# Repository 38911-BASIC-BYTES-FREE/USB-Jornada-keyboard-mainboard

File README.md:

Jornada keyboard adapter for using it as a USB HID Keyboard.
Compile it and upload in Arduino choosing Arduino Micro board.
Modification of https://github.com/RasmusB/USB-Keyboard-Adapter .
Used in project https://www.thingiverse.com/thing:6938611 .
PCB project in the folder Jornada_keyboard_mainboard .

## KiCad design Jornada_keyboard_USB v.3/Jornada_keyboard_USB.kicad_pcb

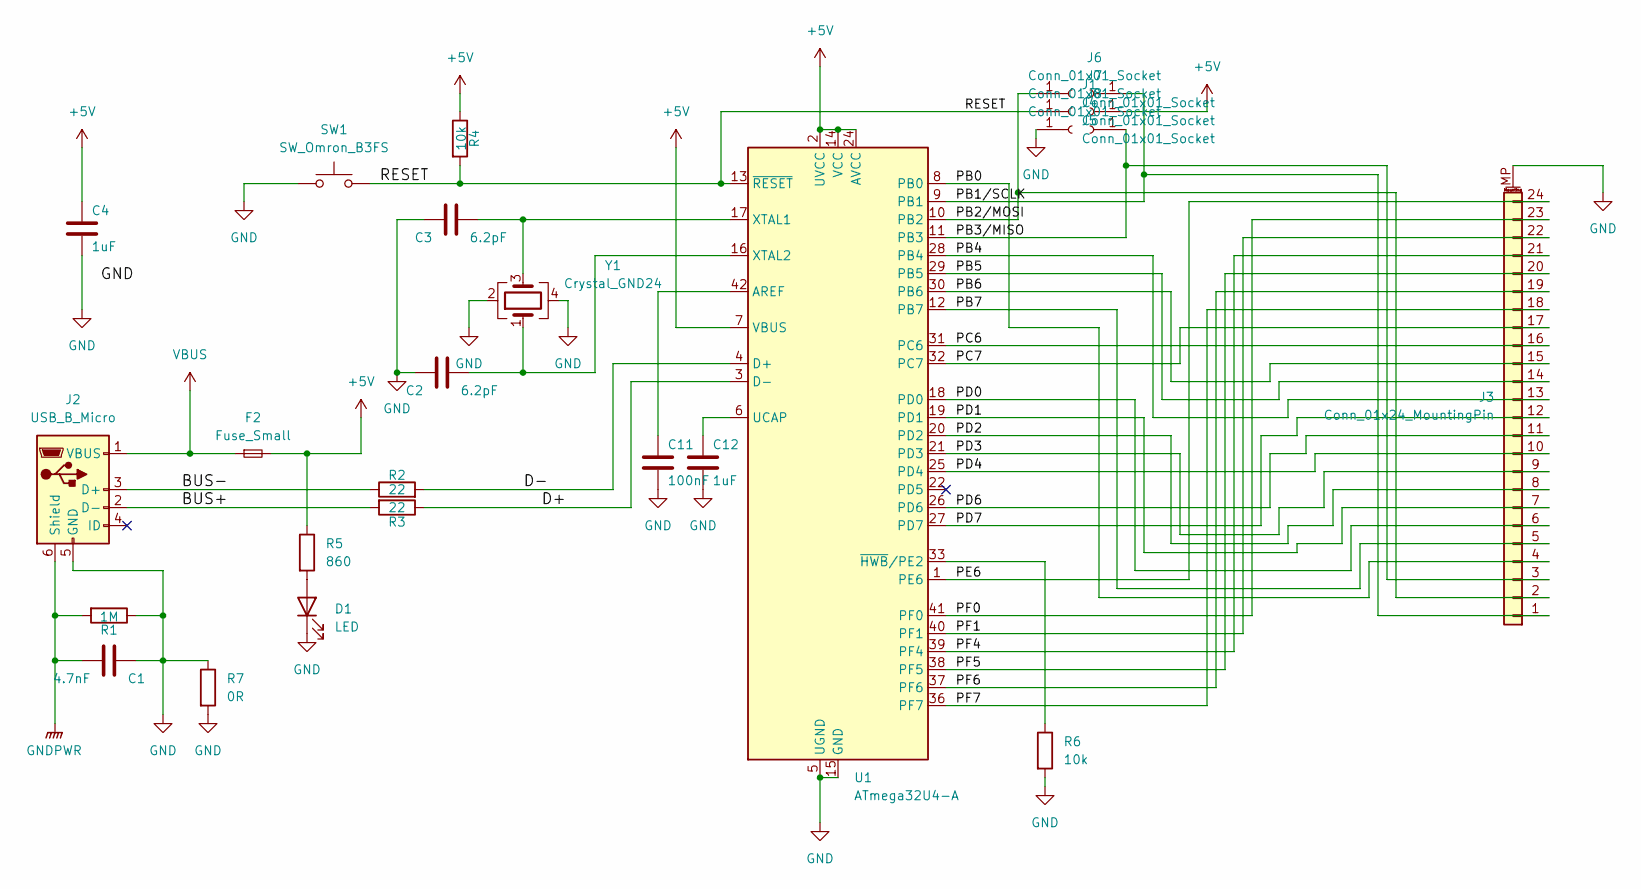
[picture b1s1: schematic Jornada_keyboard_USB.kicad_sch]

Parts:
C1: 4.7nF; C_1206_3216Metric; MPN 0402B472K500NT; JLCPCB C1538
C2, C3: 6.2pF; C_1206_3216Metric; MPN CC0402CRNPO9BN6R2; JLCPCB C325456
C4, C12: 1uF; C_1206_3216Metric; MPN CL05A105KA5NQNC; JLCPCB C52923
C11: 100nF; C_1206_3216Metric; MPN CL05B104KO5NNNC; JLCPCB C1525
D1: LED; LED_1206_3216Metric
F2: Fuse_Small; Fuse_1206_3216Metric
J1, J4, J5, J6, J7, J8: Conn_01x01_Socket; SolderWirePad_1x01_SMD_1x2mm
J2: USB_B_Micro; USB_Micro-B_Amphenol_10104110_Horizontal
J3: Conn_01x24_MountingPin; TE_2-84952-4_1x24-1MP_P1.0mm_Horizontal
R1: 1M; R_1206_3216Metric; MPN 0402WGF1004TCE; JLCPCB C26083
R2, R3: 22; R_1206_3216Metric; MPN 0402WGF220JTCE; JLCPCB C25092
R4: 10k; R_1206_3216Metric; MPN 0402WGF1002TCE; JLCPCB C25744
R5: 860; R_1206_3216Metric
R6: 10k; R_1206_3216Metric
R7: 0R; R_1206_3216Metric
SW1: SW_Omron_B3FS; SW_SPST_PTS645
U1: ATmega32U4-A; TQFP-44_10x10mm_P0.8mm
Y1: Crystal_GND24; Crystal_SMD_3225-4Pin_3.2x2.5mm_HandSoldering

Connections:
+5V: C4.1, F2.2, J7.1, R4.1, R5.1, U1.2 (UVCC), U1.7 (VBUS), U1.14 (VCC), U1.24 (AVCC), U1.34 (VCC), U1.44 (AVCC)
/BUS+: J2.2 (D-), R3.2
/BUS-: J2.3 (D+), R2.1
/D+: R3.1, U1.3 (D-)
/D-: R2.2, U1.4 (D+)
/PB0: J3.4, U1.8 (PB0)
/PB1/SCLK: J3.1, J6.1, U1.9 (PB1)
/PB2/MOSI: J1.1, J3.2, U1.10 (PB2)
/PB3/MISO: J3.3, J8.1, U1.11 (PB3)
/PB4: J3.13, U1.28 (PB4)
/PB5: J3.14, U1.29 (PB5)
/PB6: J3.15, U1.30 (PB6)
/PB7: J3.5, U1.12 (PB7)
/PC6: J3.16, U1.31 (PC6)
/PC7: J3.17, U1.32 (PC7)
/PD0: J3.6, U1.18 (PD0)
/PD1: J3.7, U1.19 (PD1)
/PD2: J3.8, U1.20 (PD2)
/PD3: J3.9, U1.21 (PD3)
/PD4: J3.10, U1.25 (PD4)
/PD6: J3.11, U1.26 (PD6)
/PD7: J3.12, U1.27 (PD7)
/PE6: J3.24, U1.1 (PE6)
/PF0: J3.23, U1.41 (PF0)
/PF1: J3.22, U1.40 (PF1)
/PF4: J3.21, U1.39 (PF4)
/PF5: J3.20, U1.38 (PF5)
/PF6: J3.19, U1.37 (PF6)
/PF7: J3.18, U1.36 (PF7)
/RESET: J4.1, R4.2, SW1.2, U1.13 (~RESET)
GND: C1.1, C2.2, C3.2, C4.2, C11.2, C12.2, D1.1 (K), J2.5 (GND), J3.MP (MountPin), J5.1, R1.1, R6.2, R7.1, R7.2, SW1.1, U1.5 (UGND), U1.15 (GND), U1.23 (GND), U1.35 (GND), U1.43 (GND), Y1.2, Y1.4
GNDPWR: C1.2, J2.6 (Shield), R1.2
unnamed: D1.2 (A), R5.2
unnamed: C11.1, U1.42 (AREF)
unnamed: C12.1, U1.6 (UCAP)
unnamed: C3.1, U1.17 (XTAL1), Y1.3
unnamed: C2.1, U1.16 (XTAL2), Y1.1
unnamed: R6.1, U1.33 (~HWB/PE2)
VBUS: F2.1, J2.1 (VBUS)

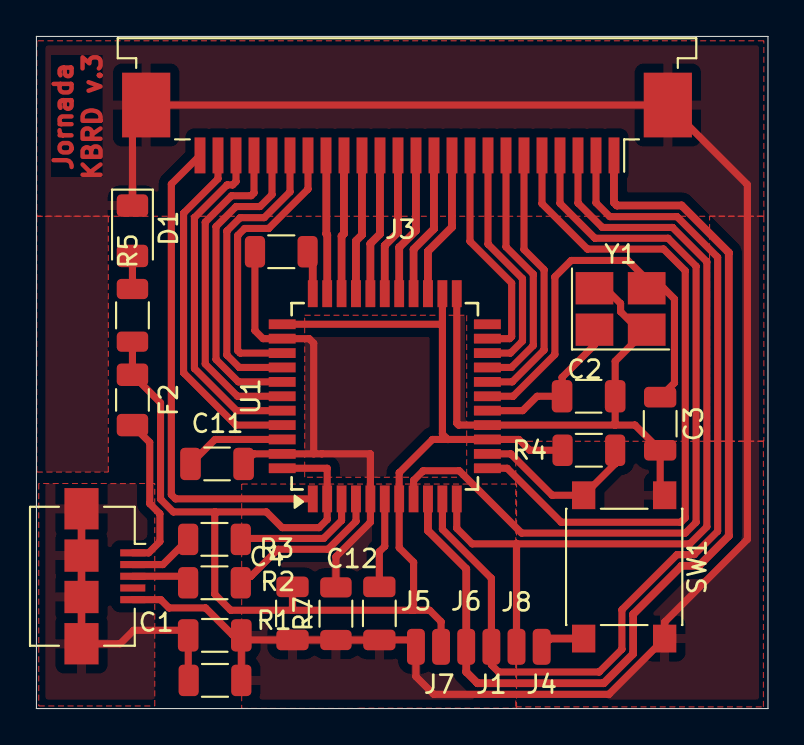
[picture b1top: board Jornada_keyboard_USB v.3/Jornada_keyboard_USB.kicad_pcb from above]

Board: 2 copper layers, 40.6 x 37.3 mm, 26 parts (0 on the bottom side), 39 nets.

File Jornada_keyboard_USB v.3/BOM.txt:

"Reference","Value","Datasheet","Footprint","Qty","DNP"
"C1","4.7nF","","Capacitor_SMD:C_1206_3216Metric","1",""
"C2,C3","6.2pF","","Capacitor_SMD:C_1206_3216Metric","2",""
"C4,C12","1uF","","Capacitor_SMD:C_1206_3216Metric","2",""
"C11","100nF","","Capacitor_SMD:C_1206_3216Metric","1",""
"D1","LED","~","LED_SMD:LED_1206_3216Metric","1",""
"F2","Fuse_Small","~","Fuse:Fuse_1206_3216Metric","1",""
"J1,J4,J5,J6,J7,J8","Conn_01x01_Socket","~","Connector_Wire:SolderWirePad_1x01_SMD_1x2mm","6",""
"J2","USB_B_Micro","~","Connector_USB:USB_Micro-B_Amphenol_10104110_Horizontal","1",""
"J3","Conn_01x24_MountingPin","~","Connector_FFC-FPC:TE_2-84952-4_1x24-1MP_P1.0mm_Horizontal","1",""
"R1","1M","","Resistor_SMD:R_1206_3216Metric","1",""
"R2,R3","22","","Resistor_SMD:R_1206_3216Metric","2",""
"R4,R6","10k","~","Resistor_SMD:R_1206_3216Metric","2",""
"R5","R","~","Resistor_SMD:R_1206_3216Metric","1",""
"R7","0R","~","Resistor_SMD:R_1206_3216Metric","1",""
"SW1","SW_Omron_B3FS","https://omronfs.omron.com/en_US/ecb/products/pdf/en-b3fs.pdf","Button_Switch_SMD:SW_SPST_PTS645","1",""
"U1","ATmega32U4-A","http://ww1.microchip.com/downloads/en/DeviceDoc/Atmel-7766-8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","Package_QFP:TQFP-44_10x10mm_P0.8mm","1",""
"Y1","Crystal_GND24","~","Crystal:Crystal_SMD_3225-4Pin_3.2x2.5mm_HandSoldering","1",""

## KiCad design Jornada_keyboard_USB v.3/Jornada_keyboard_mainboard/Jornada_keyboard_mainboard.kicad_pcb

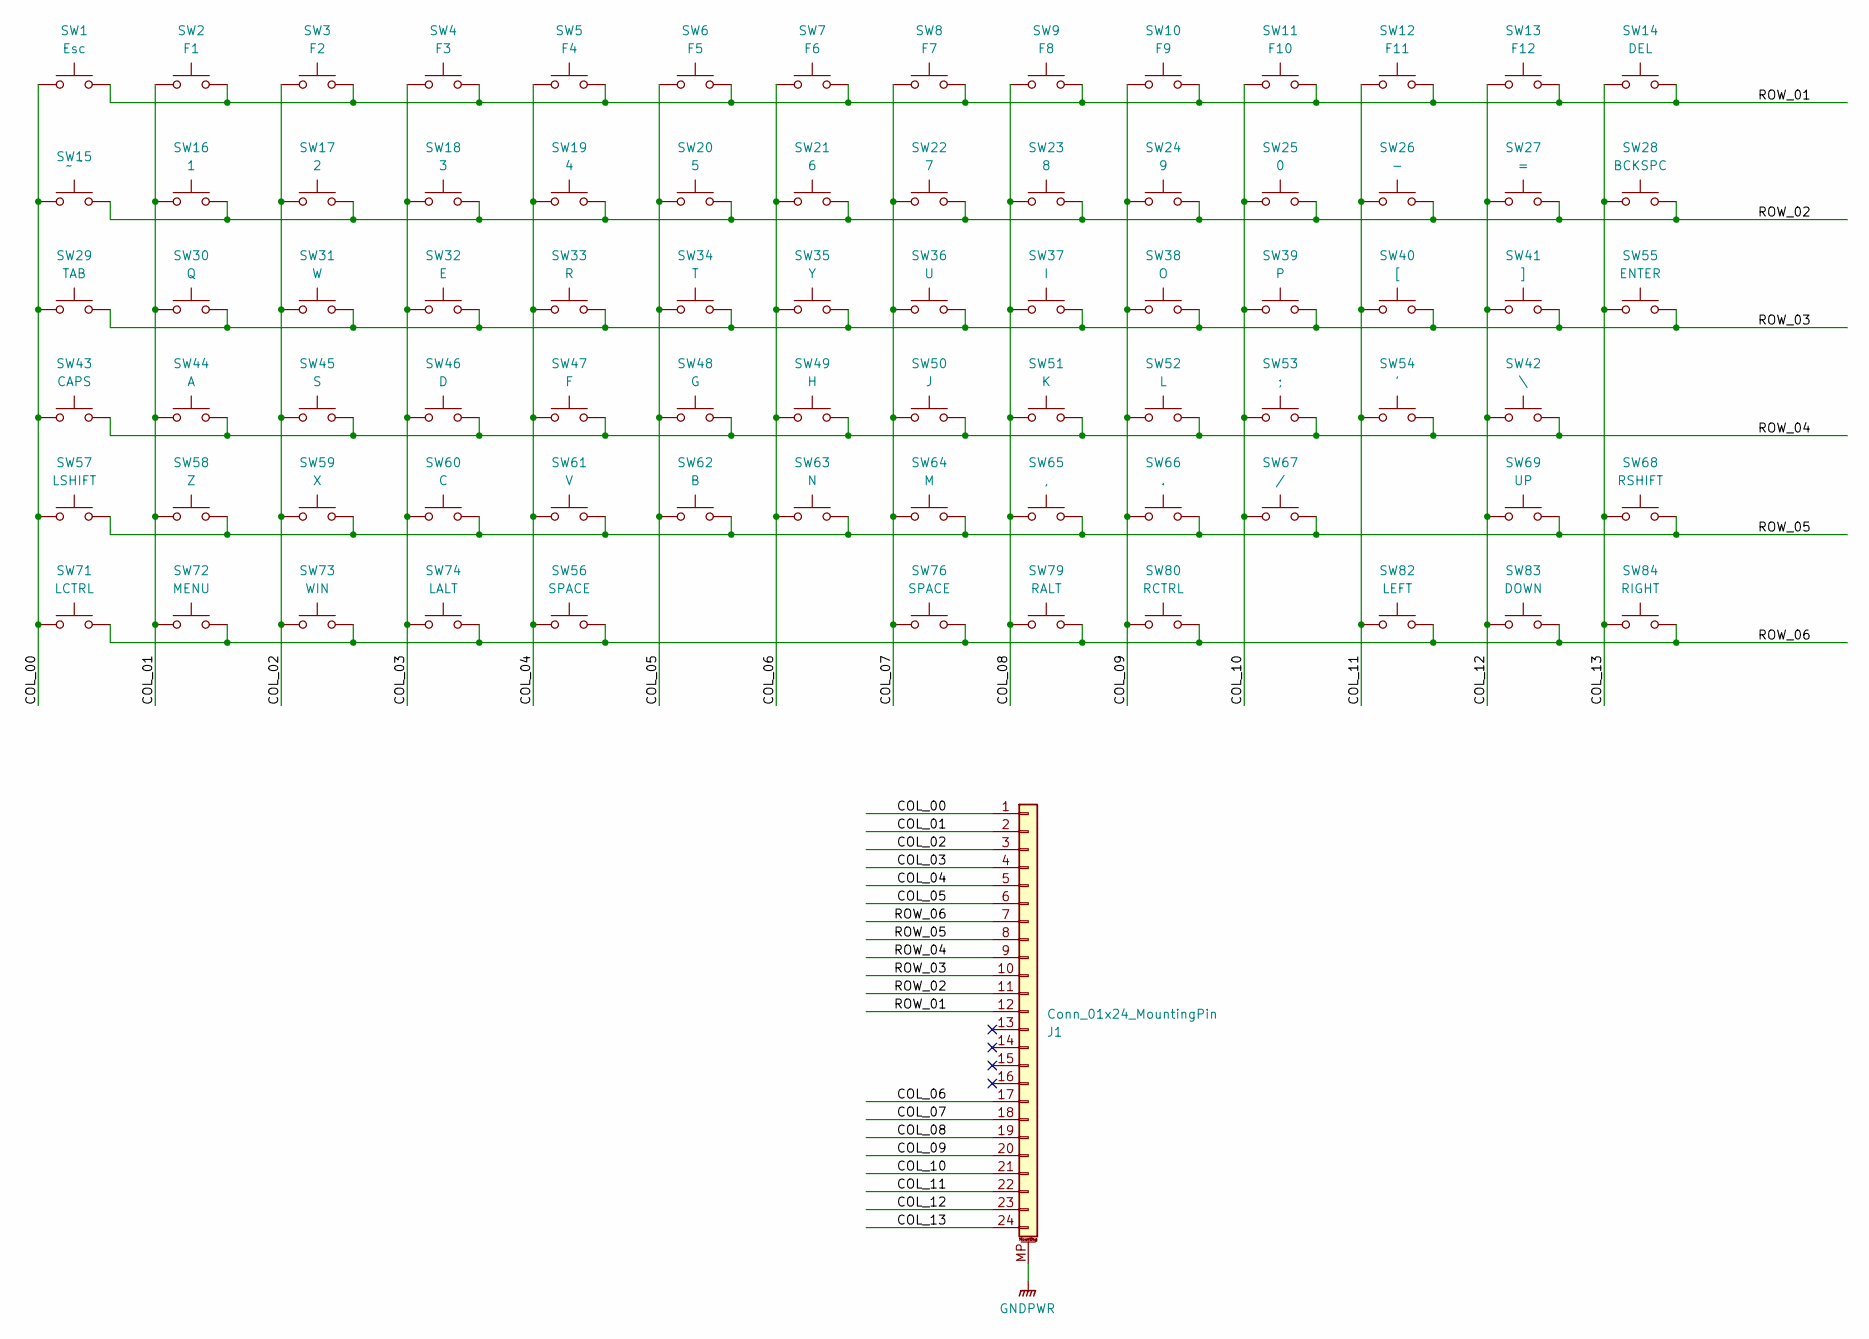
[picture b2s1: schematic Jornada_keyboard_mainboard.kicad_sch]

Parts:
J1: Conn_01x24_MountingPin; TE_2-84952-4_1x24-1MP_P1.0mm_Horizontal
SW1: Esc; SW_SPST_PTS647_Sx38
SW2: F1; SW_SPST_PTS647_Sx38
SW3: F2; SW_SPST_PTS647_Sx38
SW4: F3; SW_SPST_PTS647_Sx38
SW5: F4; SW_SPST_PTS647_Sx38
SW6: F5; SW_SPST_PTS647_Sx38
SW7: F6; SW_SPST_PTS647_Sx38
SW8: F7; SW_SPST_PTS647_Sx38
SW9: F8; SW_SPST_PTS647_Sx38
SW10: F9; SW_SPST_PTS647_Sx38
SW11: F10; SW_SPST_PTS647_Sx38
SW12: F11; SW_SPST_PTS647_Sx38
SW13: F12; SW_SPST_PTS647_Sx38
SW14: DEL; SW_SPST_PTS647_Sx38
SW15: ~ `; SW_SPST_PTS647_Sx38
SW16: 1; SW_SPST_PTS647_Sx38
SW17: 2; SW_SPST_PTS647_Sx38
SW18: 3; SW_SPST_PTS647_Sx38
SW19: 4; SW_SPST_PTS647_Sx38
SW20: 5; SW_SPST_PTS647_Sx38
SW21: 6; SW_SPST_PTS647_Sx38
SW22: 7; SW_SPST_PTS647_Sx38
SW23: 8; SW_SPST_PTS647_Sx38
SW24: 9; SW_SPST_PTS647_Sx38
SW25: 0; SW_SPST_PTS647_Sx38
SW26: -; SW_SPST_PTS647_Sx38
SW27: =; SW_SPST_PTS647_Sx38
SW28: BCKSPC; SW_SPST_PTS647_Sx38
SW29: TAB; SW_SPST_PTS647_Sx38
SW30: Q; SW_SPST_PTS647_Sx38
SW31: W; SW_SPST_PTS647_Sx38
SW32: E; SW_SPST_PTS647_Sx38
SW33: R; SW_SPST_PTS647_Sx38
SW34: T; SW_SPST_PTS647_Sx38
SW35: Y; SW_SPST_PTS647_Sx38
SW36: U; SW_SPST_PTS647_Sx38
SW37: I; SW_SPST_PTS647_Sx38
SW38: O; SW_SPST_PTS647_Sx38
SW39: P; SW_SPST_PTS647_Sx38
SW40: [; SW_SPST_PTS647_Sx38
SW41: ]; SW_SPST_PTS647_Sx38
SW42: \; SW_SPST_PTS647_Sx38
SW43: CAPS; SW_SPST_PTS647_Sx38
SW44: A; SW_SPST_PTS647_Sx38
SW45: S; SW_SPST_PTS647_Sx38
SW46: D; SW_SPST_PTS647_Sx38
SW47: F; SW_SPST_PTS647_Sx38
SW48: G; SW_SPST_PTS647_Sx38
SW49: H; SW_SPST_PTS647_Sx38
SW50: J; SW_SPST_PTS647_Sx38
SW51: K; SW_SPST_PTS647_Sx38
SW52: L; SW_SPST_PTS647_Sx38
SW53: ;; SW_SPST_PTS647_Sx38
SW54: '; SW_SPST_PTS647_Sx38
SW55: ENTER; SW_SPST_PTS647_Sx38
SW56, SW76: SPACE; SW_SPST_PTS647_Sx38
SW57: LSHIFT; SW_SPST_PTS647_Sx38
SW58: Z; SW_SPST_PTS647_Sx38
SW59: X; SW_SPST_PTS647_Sx38
SW60: C; SW_SPST_PTS647_Sx38
SW61: V; SW_SPST_PTS647_Sx38
SW62: B; SW_SPST_PTS647_Sx38
SW63: N; SW_SPST_PTS647_Sx38
SW64: M; SW_SPST_PTS647_Sx38
SW65: ,; SW_SPST_PTS647_Sx38
SW66: .; SW_SPST_PTS647_Sx38
SW67: /; SW_SPST_PTS647_Sx38
SW68: RSHIFT; SW_SPST_PTS647_Sx38
SW69: UP; SW_SPST_PTS647_Sx38
SW71: LCTRL; SW_SPST_PTS647_Sx38
SW72: MENU; SW_SPST_PTS647_Sx38
SW73: WIN; SW_SPST_PTS647_Sx38
SW74: LALT; SW_SPST_PTS647_Sx38
SW79: RALT; SW_SPST_PTS647_Sx38
SW80: RCTRL; SW_SPST_PTS647_Sx38
SW82: LEFT; SW_SPST_PTS647_Sx38
SW83: DOWN; SW_SPST_PTS647_Sx38
SW84: RIGHT; SW_SPST_PTS647_Sx38

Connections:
/COL_00: J1.1, SW1.1, SW15.1, SW29.1, SW43.1, SW57.1, SW71.1
/COL_01: J1.2, SW2.1, SW16.1, SW30.1, SW44.1, SW58.1, SW72.1
/COL_02: J1.3, SW3.1, SW17.1, SW31.1, SW45.1, SW59.1, SW73.1
/COL_03: J1.4, SW4.1, SW18.1, SW32.1, SW46.1, SW60.1, SW74.1
/COL_04: J1.5, SW5.1, SW19.1, SW33.1, SW47.1, SW56.1, SW61.1
/COL_05: J1.6, SW6.1, SW20.1, SW34.1, SW48.1, SW62.1
/COL_06: J1.17, SW7.1, SW21.1, SW35.1, SW49.1, SW63.1
/COL_07: J1.18, SW8.1, SW22.1, SW36.1, SW50.1, SW64.1, SW76.1
/COL_08: J1.19, SW9.1, SW23.1, SW37.1, SW51.1, SW65.1, SW79.1
/COL_09: J1.20, SW10.1, SW24.1, SW38.1, SW52.1, SW66.1, SW80.1
/COL_10: J1.21, SW11.1, SW25.1, SW39.1, SW53.1, SW67.1
/COL_11: J1.22, SW12.1, SW26.1, SW40.1, SW54.1, SW82.1
/COL_12: J1.23, SW13.1, SW27.1, SW41.1, SW42.1, SW69.1, SW83.1
/COL_13: J1.24, SW14.1, SW28.1, SW55.1, SW68.1, SW84.1
/ROW_01: J1.12, SW1.2, SW2.2, SW3.2, SW4.2, SW5.2, SW6.2, SW7.2, SW8.2, SW9.2, SW10.2, SW11.2, SW12.2, SW13.2, SW14.2
/ROW_02: J1.11, SW15.2, SW16.2, SW17.2, SW18.2, SW19.2, SW20.2, SW21.2, SW22.2, SW23.2, SW24.2, SW25.2, SW26.2, SW27.2, SW28.2
/ROW_03: J1.10, SW29.2, SW30.2, SW31.2, SW32.2, SW33.2, SW34.2, SW35.2, SW36.2, SW37.2, SW38.2, SW39.2, SW40.2, SW41.2, SW55.2
/ROW_04: J1.9, SW42.2, SW43.2, SW44.2, SW45.2, SW46.2, SW47.2, SW48.2, SW49.2, SW50.2, SW51.2, SW52.2, SW53.2, SW54.2
/ROW_05: J1.8, SW57.2, SW58.2, SW59.2, SW60.2, SW61.2, SW62.2, SW63.2, SW64.2, SW65.2, SW66.2, SW67.2, SW68.2, SW69.2
/ROW_06: J1.7, SW56.2, SW71.2, SW72.2, SW73.2, SW74.2, SW76.2, SW79.2, SW80.2, SW82.2, SW83.2, SW84.2
GNDPWR: J1.MP (MountPin)

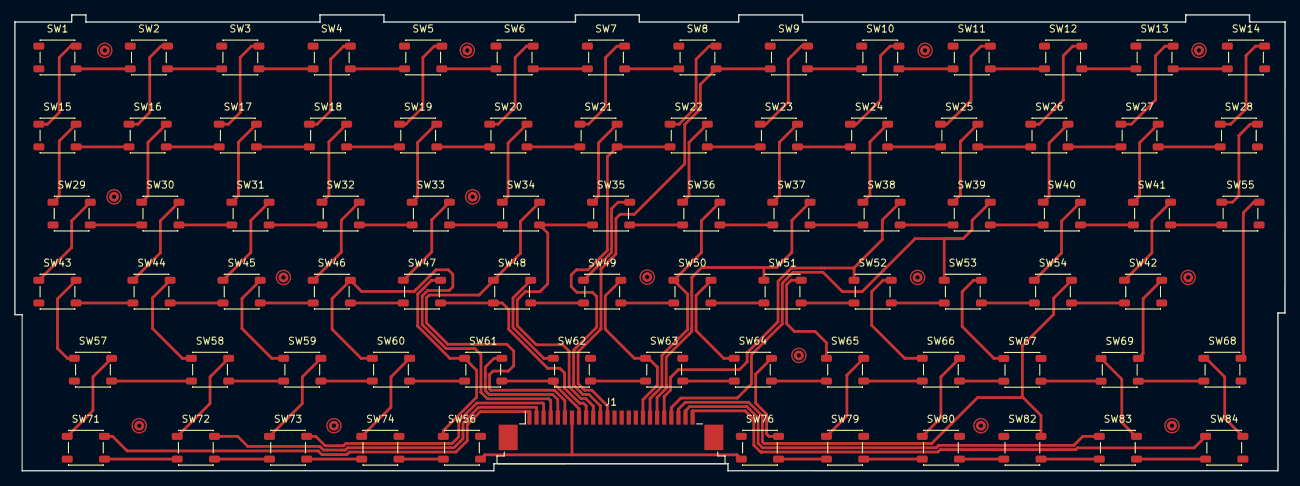
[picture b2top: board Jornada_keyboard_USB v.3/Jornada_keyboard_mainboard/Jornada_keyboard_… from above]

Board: 2 copper layers, 179.0 x 64.2 mm, 80 parts (0 on the bottom side), 20 nets.

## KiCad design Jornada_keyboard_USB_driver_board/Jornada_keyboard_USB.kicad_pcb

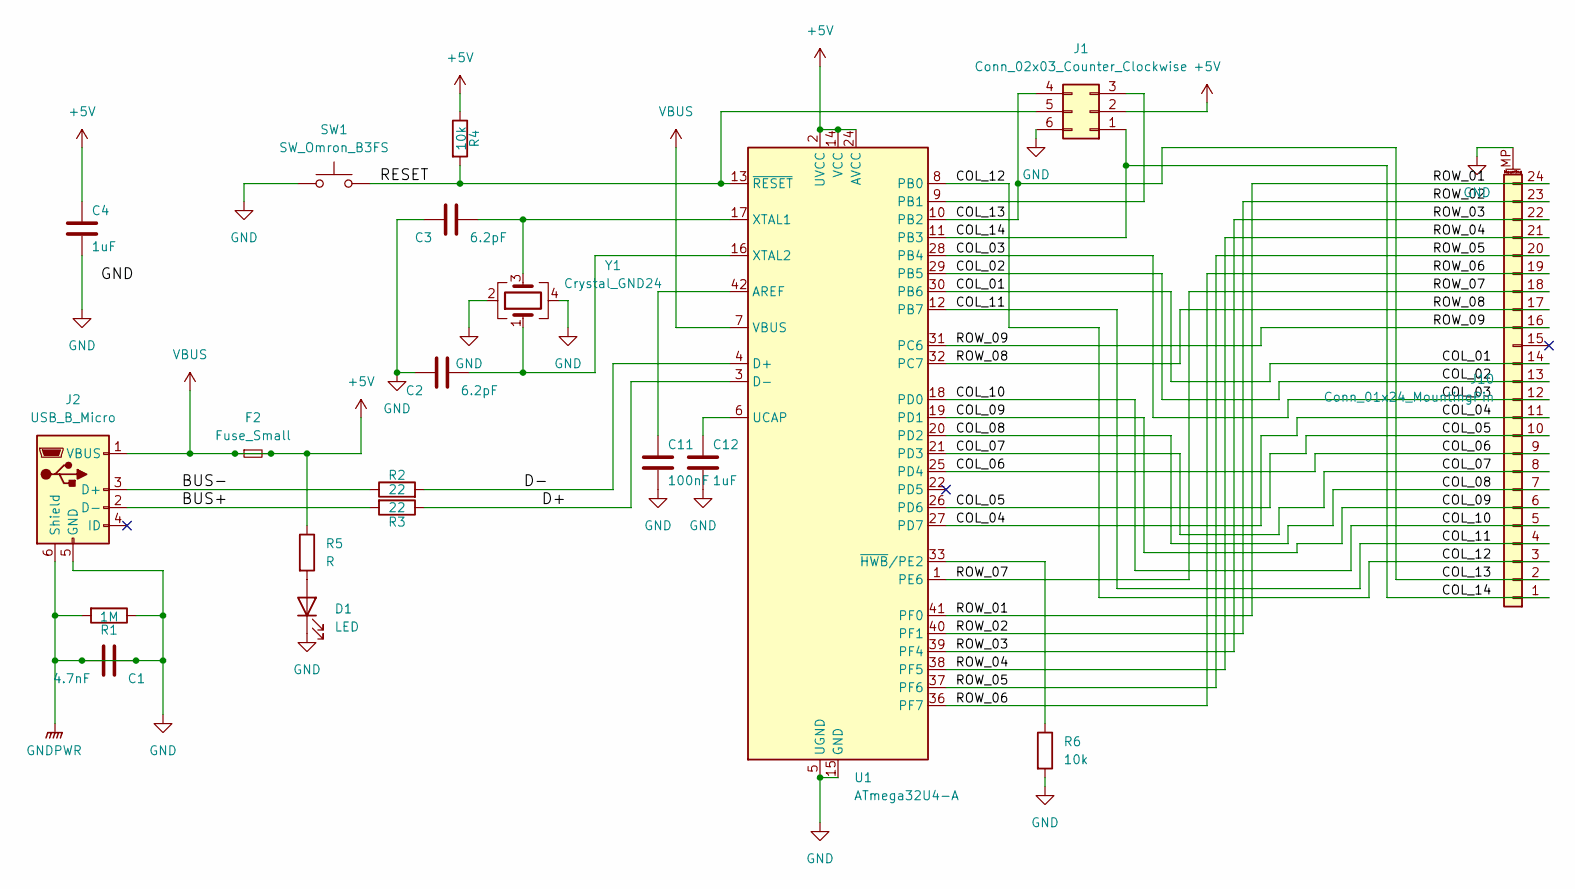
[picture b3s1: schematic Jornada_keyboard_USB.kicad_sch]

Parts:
C1: 4.7nF; C_1206_3216Metric; MPN 0402B472K500NT; JLCPCB C1538
C2, C3: 6.2pF; C_1206_3216Metric; MPN CC0402CRNPO9BN6R2; JLCPCB C325456
C4, C12: 1uF; C_1206_3216Metric; MPN CL05A105KA5NQNC; JLCPCB C52923
C11: 100nF; C_1206_3216Metric; MPN CL05B104KO5NNNC; JLCPCB C1525
D1: LED; LED_1206_3216Metric
F2: Fuse_Small; Fuse_1206_3216Metric
J1: Conn_02x03_Counter_Clockwise; PinHeader_2x03_P2.54mm_Vertical
J2: USB_B_Micro; USB_Micro-B_Amphenol_10104110_Horizontal
J10: Conn_01x24_MountingPin; Molex_200528-0240_1x24-1MP_P1.00mm_Horizontal
R1: 1M; R_1206_3216Metric; MPN 0402WGF1004TCE; JLCPCB C26083
R2, R3: 22; R_1206_3216Metric; MPN 0402WGF220JTCE; JLCPCB C25092
R4: 10k; R_1206_3216Metric; MPN 0402WGF1002TCE; JLCPCB C25744
R5: R; R_1206_3216Metric
R6: 10k; R_1206_3216Metric
SW1: SW_Omron_B3FS; SW_SPST_PTS645
U1: ATmega32U4-A; TQFP-44_10x10mm_P0.8mm
Y1: Crystal_GND24; Crystal_SMD_3225-4Pin_3.2x2.5mm_HandSoldering

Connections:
+5V: C4.1, F2.1, F2.2, J1.2, J2.1 (VBUS), R4.1, R5.1, U1.2 (UVCC), U1.7 (VBUS), U1.14 (VCC), U1.24 (AVCC), U1.34 (VCC), U1.44 (AVCC)
/BUS+: J2.2 (D-), R3.2
/BUS-: J2.3 (D+), R2.1
/D+: R3.1, U1.3 (D-)
/D-: R2.2, U1.4 (D+)
/RESET: J1.5, R4.2, SW1.2, U1.13 (~RESET)
GND: C1.1, C1.2, C2.2, C3.2, C4.2, C11.2, C12.2, D1.1 (K), J1.6, J2.5 (GND), J2.6 (Shield), J10.MP (MountPin), R1.1, R1.2, R6.2, SW1.1, U1.5 (UGND), U1.15 (GND), U1.23 (GND), U1.35 (GND), U1.43 (GND), Y1.2, Y1.4
unnamed: D1.2 (A), R5.2
unnamed: J1.1, J10.1, U1.11 (PB3)
unnamed: J1.3, U1.9 (PB1)
unnamed: J1.4, J10.2, U1.10 (PB2)
unnamed: J10.3, U1.8 (PB0)
unnamed: J10.4, U1.12 (PB7)
unnamed: J10.5, U1.18 (PD0)
unnamed: J10.6, U1.19 (PD1)
unnamed: J10.7, U1.20 (PD2)
unnamed: J10.8, U1.21 (PD3)
unnamed: J10.9, U1.25 (PD4)
unnamed: J10.10, U1.26 (PD6)
unnamed: J10.11, U1.27 (PD7)
unnamed: J10.12, U1.28 (PB4)
unnamed: J10.13, U1.29 (PB5)
unnamed: J10.14, U1.30 (PB6)
unnamed: J10.16, U1.31 (PC6)
unnamed: J10.17, U1.32 (PC7)
unnamed: J10.18, U1.1 (PE6)
unnamed: J10.19, U1.36 (PF7)
unnamed: J10.20, U1.37 (PF6)
unnamed: J10.21, U1.38 (PF5)
unnamed: J10.22, U1.39 (PF4)
unnamed: J10.23, U1.40 (PF1)
unnamed: J10.24, U1.41 (PF0)
unnamed: C11.1, U1.42 (AREF)
unnamed: C12.1, U1.6 (UCAP)
unnamed: C3.1, U1.17 (XTAL1), Y1.3
unnamed: C2.1, U1.16 (XTAL2), Y1.1
unnamed: R6.1, U1.33 (~HWB/PE2)

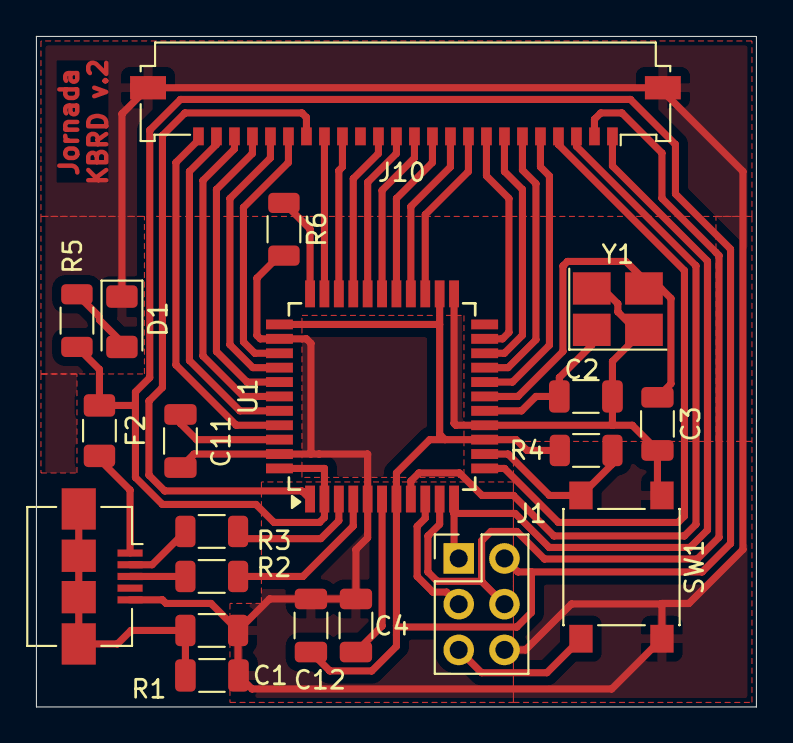
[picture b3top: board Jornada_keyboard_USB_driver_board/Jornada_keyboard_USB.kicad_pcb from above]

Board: 2 copper layers, 40.0 x 37.2 mm, 20 parts (0 on the bottom side), 37 nets.

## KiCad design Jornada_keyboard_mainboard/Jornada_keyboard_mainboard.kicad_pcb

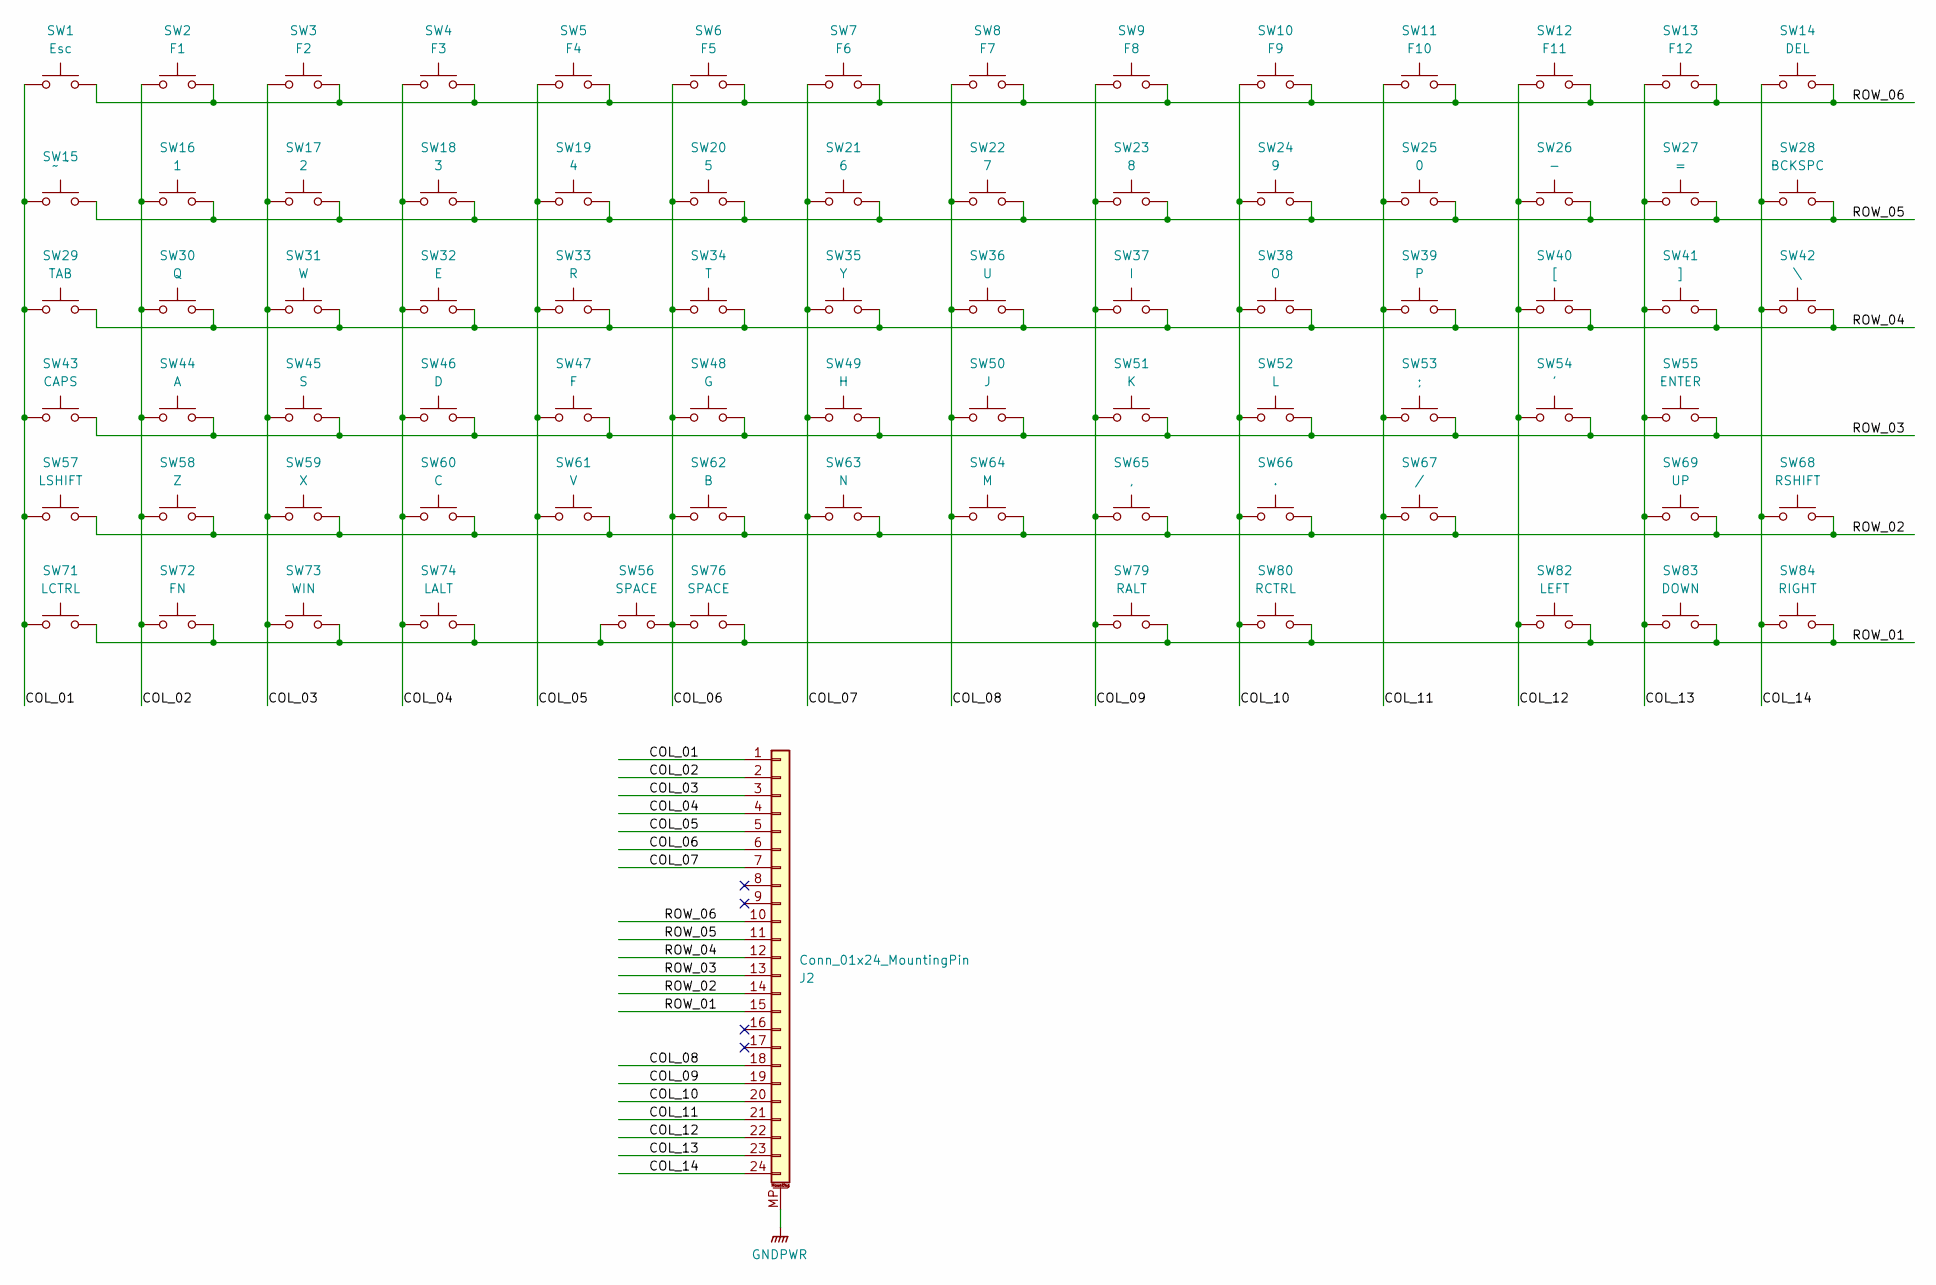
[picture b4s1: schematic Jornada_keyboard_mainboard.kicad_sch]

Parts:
J2: Conn_01x24_MountingPin; Molex_200528-0240_1x24-1MP_P1.00mm_Horizontal
SW1: Esc; SW_SPST_Omron_B3FS-100xP
SW2: F1; SW_SPST_Omron_B3FS-100xP
SW3: F2; SW_SPST_Omron_B3FS-100xP
SW4: F3; SW_SPST_Omron_B3FS-100xP
SW5: F4; SW_SPST_Omron_B3FS-100xP
SW6: F5; SW_SPST_Omron_B3FS-100xP
SW7: F6; SW_SPST_Omron_B3FS-100xP
SW8: F7; SW_SPST_Omron_B3FS-100xP
SW9: F8; SW_SPST_Omron_B3FS-100xP
SW10: F9; SW_SPST_Omron_B3FS-100xP
SW11: F10; SW_SPST_Omron_B3FS-100xP
SW12: F11; SW_SPST_Omron_B3FS-100xP
SW13: F12; SW_SPST_Omron_B3FS-100xP
SW14: DEL; SW_SPST_Omron_B3FS-100xP
SW15: ~ `; SW_SPST_Omron_B3FS-100xP
SW16: 1; SW_SPST_Omron_B3FS-100xP
SW17: 2; SW_SPST_Omron_B3FS-100xP
SW18: 3; SW_SPST_Omron_B3FS-100xP
SW19: 4; SW_SPST_Omron_B3FS-100xP
SW20: 5; SW_SPST_Omron_B3FS-100xP
SW21: 6; SW_SPST_Omron_B3FS-100xP
SW22: 7; SW_SPST_Omron_B3FS-100xP
SW23: 8; SW_SPST_Omron_B3FS-100xP
SW24: 9; SW_SPST_Omron_B3FS-100xP
SW25: 0; SW_SPST_Omron_B3FS-100xP
SW26: -; SW_SPST_Omron_B3FS-100xP
SW27: =; SW_SPST_Omron_B3FS-100xP
SW28: BCKSPC; SW_SPST_Omron_B3FS-100xP
SW29: TAB; SW_SPST_Omron_B3FS-100xP
SW30: Q; SW_SPST_Omron_B3FS-100xP
SW31: W; SW_SPST_Omron_B3FS-100xP
SW32: E; SW_SPST_Omron_B3FS-100xP
SW33: R; SW_SPST_Omron_B3FS-100xP
SW34: T; SW_SPST_Omron_B3FS-100xP
SW35: Y; SW_SPST_Omron_B3FS-100xP
SW36: U; SW_SPST_Omron_B3FS-100xP
SW37: I; SW_SPST_Omron_B3FS-100xP
SW38: O; SW_SPST_Omron_B3FS-100xP
SW39: P; SW_SPST_Omron_B3FS-100xP
SW40: [; SW_SPST_Omron_B3FS-100xP
SW41: ]; SW_SPST_Omron_B3FS-100xP
SW42: \; SW_SPST_Omron_B3FS-100xP
SW43: CAPS; SW_SPST_Omron_B3FS-100xP
SW44: A; SW_SPST_Omron_B3FS-100xP
SW45: S; SW_SPST_Omron_B3FS-100xP
SW46: D; SW_SPST_Omron_B3FS-100xP
SW47: F; SW_SPST_Omron_B3FS-100xP
SW48: G; SW_SPST_Omron_B3FS-100xP
SW49: H; SW_SPST_Omron_B3FS-100xP
SW50: J; SW_SPST_Omron_B3FS-100xP
SW51: K; SW_SPST_Omron_B3FS-100xP
SW52: L; SW_SPST_Omron_B3FS-100xP
SW53: ;; SW_SPST_Omron_B3FS-100xP
SW54: '; SW_SPST_Omron_B3FS-100xP
SW55: ENTER; SW_SPST_Omron_B3FS-100xP
SW56, SW76: SPACE; SW_SPST_Omron_B3FS-100xP
SW57: LSHIFT; SW_SPST_Omron_B3FS-100xP
SW58: Z; SW_SPST_Omron_B3FS-100xP
SW59: X; SW_SPST_Omron_B3FS-100xP
SW60: C; SW_SPST_Omron_B3FS-100xP
SW61: V; SW_SPST_Omron_B3FS-100xP
SW62: B; SW_SPST_Omron_B3FS-100xP
SW63: N; SW_SPST_Omron_B3FS-100xP
SW64: M; SW_SPST_Omron_B3FS-100xP
SW65: ,; SW_SPST_Omron_B3FS-100xP
SW66: .; SW_SPST_Omron_B3FS-100xP
SW67: /; SW_SPST_Omron_B3FS-100xP
SW68: RSHIFT; SW_SPST_Omron_B3FS-100xP
SW69: UP; SW_SPST_Omron_B3FS-100xP
SW71: LCTRL; SW_SPST_Omron_B3FS-100xP
SW72: FN; SW_SPST_Omron_B3FS-100xP
SW73: WIN; SW_SPST_Omron_B3FS-100xP
SW74: LALT; SW_SPST_Omron_B3FS-100xP
SW79: RALT; SW_SPST_Omron_B3FS-100xP
SW80: RCTRL; SW_SPST_Omron_B3FS-100xP
SW82: LEFT; SW_SPST_Omron_B3FS-100xP
SW83: DOWN; SW_SPST_Omron_B3FS-100xP
SW84: RIGHT; SW_SPST_Omron_B3FS-100xP

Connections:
/COL_01: J2.1, SW1.1, SW15.1, SW29.1, SW43.1, SW57.1, SW71.1
/COL_02: J2.2, SW2.1, SW16.1, SW30.1, SW44.1, SW58.1, SW72.1
/COL_03: J2.3, SW3.1, SW17.1, SW31.1, SW45.1, SW59.1, SW73.1
/COL_04: J2.4, SW4.1, SW18.1, SW32.1, SW46.1, SW60.1, SW74.1
/COL_05: J2.5, SW5.1, SW19.1, SW33.1, SW47.1, SW61.1
/COL_06: J2.6, SW6.1, SW20.1, SW34.1, SW48.1, SW56.2, SW62.1, SW76.1
/COL_07: J2.7, SW7.1, SW21.1, SW35.1, SW49.1, SW63.1
/COL_08: J2.18, SW8.1, SW22.1, SW36.1, SW50.1, SW64.1
/COL_09: J2.19, SW9.1, SW23.1, SW37.1, SW51.1, SW65.1, SW79.1
/COL_10: J2.20, SW10.1, SW24.1, SW38.1, SW52.1, SW66.1, SW80.1
/COL_11: J2.21, SW11.1, SW25.1, SW39.1, SW53.1, SW67.1
/COL_12: J2.22, SW12.1, SW26.1, SW40.1, SW54.1, SW82.1
/COL_13: J2.23, SW13.1, SW27.1, SW41.1, SW55.1, SW69.1, SW83.1
/COL_14: J2.24, SW14.1, SW28.1, SW42.1, SW68.1, SW84.1
/ROW_01: J2.15, SW56.1, SW71.2, SW72.2, SW73.2, SW74.2, SW76.2, SW79.2, SW80.2, SW82.2, SW83.2, SW84.2
/ROW_02: J2.14, SW57.2, SW58.2, SW59.2, SW60.2, SW61.2, SW62.2, SW63.2, SW64.2, SW65.2, SW66.2, SW67.2, SW68.2, SW69.2
/ROW_03: J2.13, SW43.2, SW44.2, SW45.2, SW46.2, SW47.2, SW48.2, SW49.2, SW50.2, SW51.2, SW52.2, SW53.2, SW54.2, SW55.2
/ROW_04: J2.12, SW29.2, SW30.2, SW31.2, SW32.2, SW33.2, SW34.2, SW35.2, SW36.2, SW37.2, SW38.2, SW39.2, SW40.2, SW41.2, SW42.2
/ROW_05: J2.11, SW15.2, SW16.2, SW17.2, SW18.2, SW19.2, SW20.2, SW21.2, SW22.2, SW23.2, SW24.2, SW25.2, SW26.2, SW27.2, SW28.2
/ROW_06: J2.10, SW1.2, SW2.2, SW3.2, SW4.2, SW5.2, SW6.2, SW7.2, SW8.2, SW9.2, SW10.2, SW11.2, SW12.2, SW13.2, SW14.2
GNDPWR: J2.MP (MountPin)

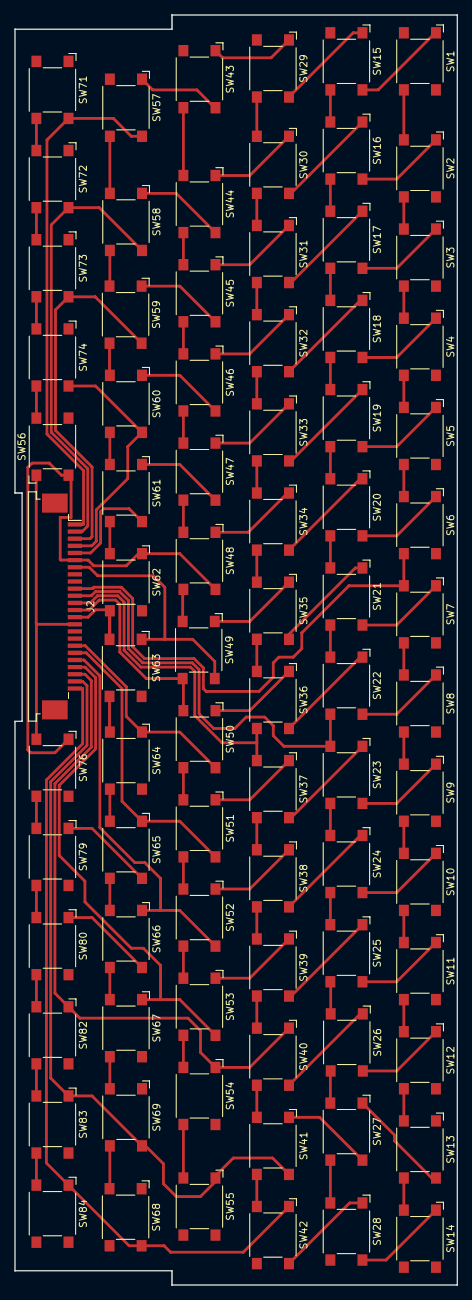
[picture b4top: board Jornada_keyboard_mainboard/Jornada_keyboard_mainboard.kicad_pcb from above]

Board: 2 copper layers, 62.0 x 178.0 mm, 80 parts (0 on the bottom side), 20 nets.

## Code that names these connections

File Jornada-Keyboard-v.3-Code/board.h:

/*
 board.h
 
 This is how the pins are connected to the keyboard
 
 */



// Standard LED is moved to pin 13 and disabled
#undef LED_BUILTIN
#define LED_BUILTIN 0
 
// See the keyboard schematic for row/col mapping
#define NROWS 6
#define NCOLS 14

#define ROW_01   8     //PB4  
#define ROW_02   9     //PB5  
#define ROW_03   10    //PB6
#define ROW_04   5     //PC6      
#define ROW_05   13    //PC7
#define ROW_06   A0    //PF7

#define COL_00   7     //PE6
#define COL_01   A5    //PF0
#define COL_02   A4    //PF1 
#define COL_03   A3    //PF4
#define COL_04   A2    //PF5
#define COL_05   A1    //PF6 
#define COL_06   0     //PD2
#define COL_07   2     //PD1
#define COL_08   3     //PD0
#define COL_09   11    //PB7
#define COL_10   SS    //PB0
#define COL_11   MISO  // PB3
#define COL_12   MOSI  // PB2
#define COL_13   SCK   //PB1

int Rows [NROWS] = {
  ROW_01,
  ROW_02,
  ROW_03,
  ROW_04,
  ROW_05,
  ROW_06
};

int Cols [NCOLS] = {
  COL_00,
  COL_01,
  COL_02,
  COL_03,
  COL_04,
  COL_05,
  COL_06,
  COL_07,
  COL_08,
  COL_09,
  COL_10,
  COL_11,
  COL_12,
  COL_13
};

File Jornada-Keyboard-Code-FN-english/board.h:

/*
 board.h
 
 This is how the pins are connected to the keyboard
 
 */



// Standard LED is moved to pin 13 and disabled
#undef LED_BUILTIN
#define LED_BUILTIN 0
 
// See the keyboard schematic for row/col mapping
#define NROWS 9
#define NCOLS 14

#define ROW_01   7 //PE6 
#define ROW_02   A5 //PF0
#define ROW_03   A4 //PF1
#define ROW_04   A3 //PF4
#define ROW_05   A2 //PF5
#define ROW_06   A1 //PF6
#define ROW_07   A0 //PF7
#define ROW_08   13 //PC7
#define ROW_09   5 //PC6

#define COL_1    9 //PB5
#define COL_2    8 //PB4
#define COL_3    6 //PD7 
#define COL_4    12 //PD6
#define COL_5    4 //PD4
#define COL_6    1 //PD3
#define COL_7    0 //PD2
#define COL_8    2 //PD1
#define COL_9    3 //PD0
#define COL_10   11 //PB7 
#define COL_11   SS //PB0
#define COL_12   MISO // PB3
#define COL_13   MOSI // PB2
#define COL_14   SCK //PB1

int Rows [NROWS] = {
  ROW_01,
  ROW_02,
  ROW_03,
  ROW_04,
  ROW_05,
  ROW_06,
  ROW_07,
  ROW_08,
  ROW_09
};

int Cols [NCOLS] = {
  COL_1,
  COL_2,
  COL_3,
  COL_4,
  COL_5,
  COL_6,
  COL_7,
  COL_8,
  COL_9,
  COL_10,
  COL_11,
  COL_12,
  COL_13,
  COL_14
};

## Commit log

2025-03-15 Add files via upload
    FN doesn't work yet, it's ignored in this code. Working on it.
